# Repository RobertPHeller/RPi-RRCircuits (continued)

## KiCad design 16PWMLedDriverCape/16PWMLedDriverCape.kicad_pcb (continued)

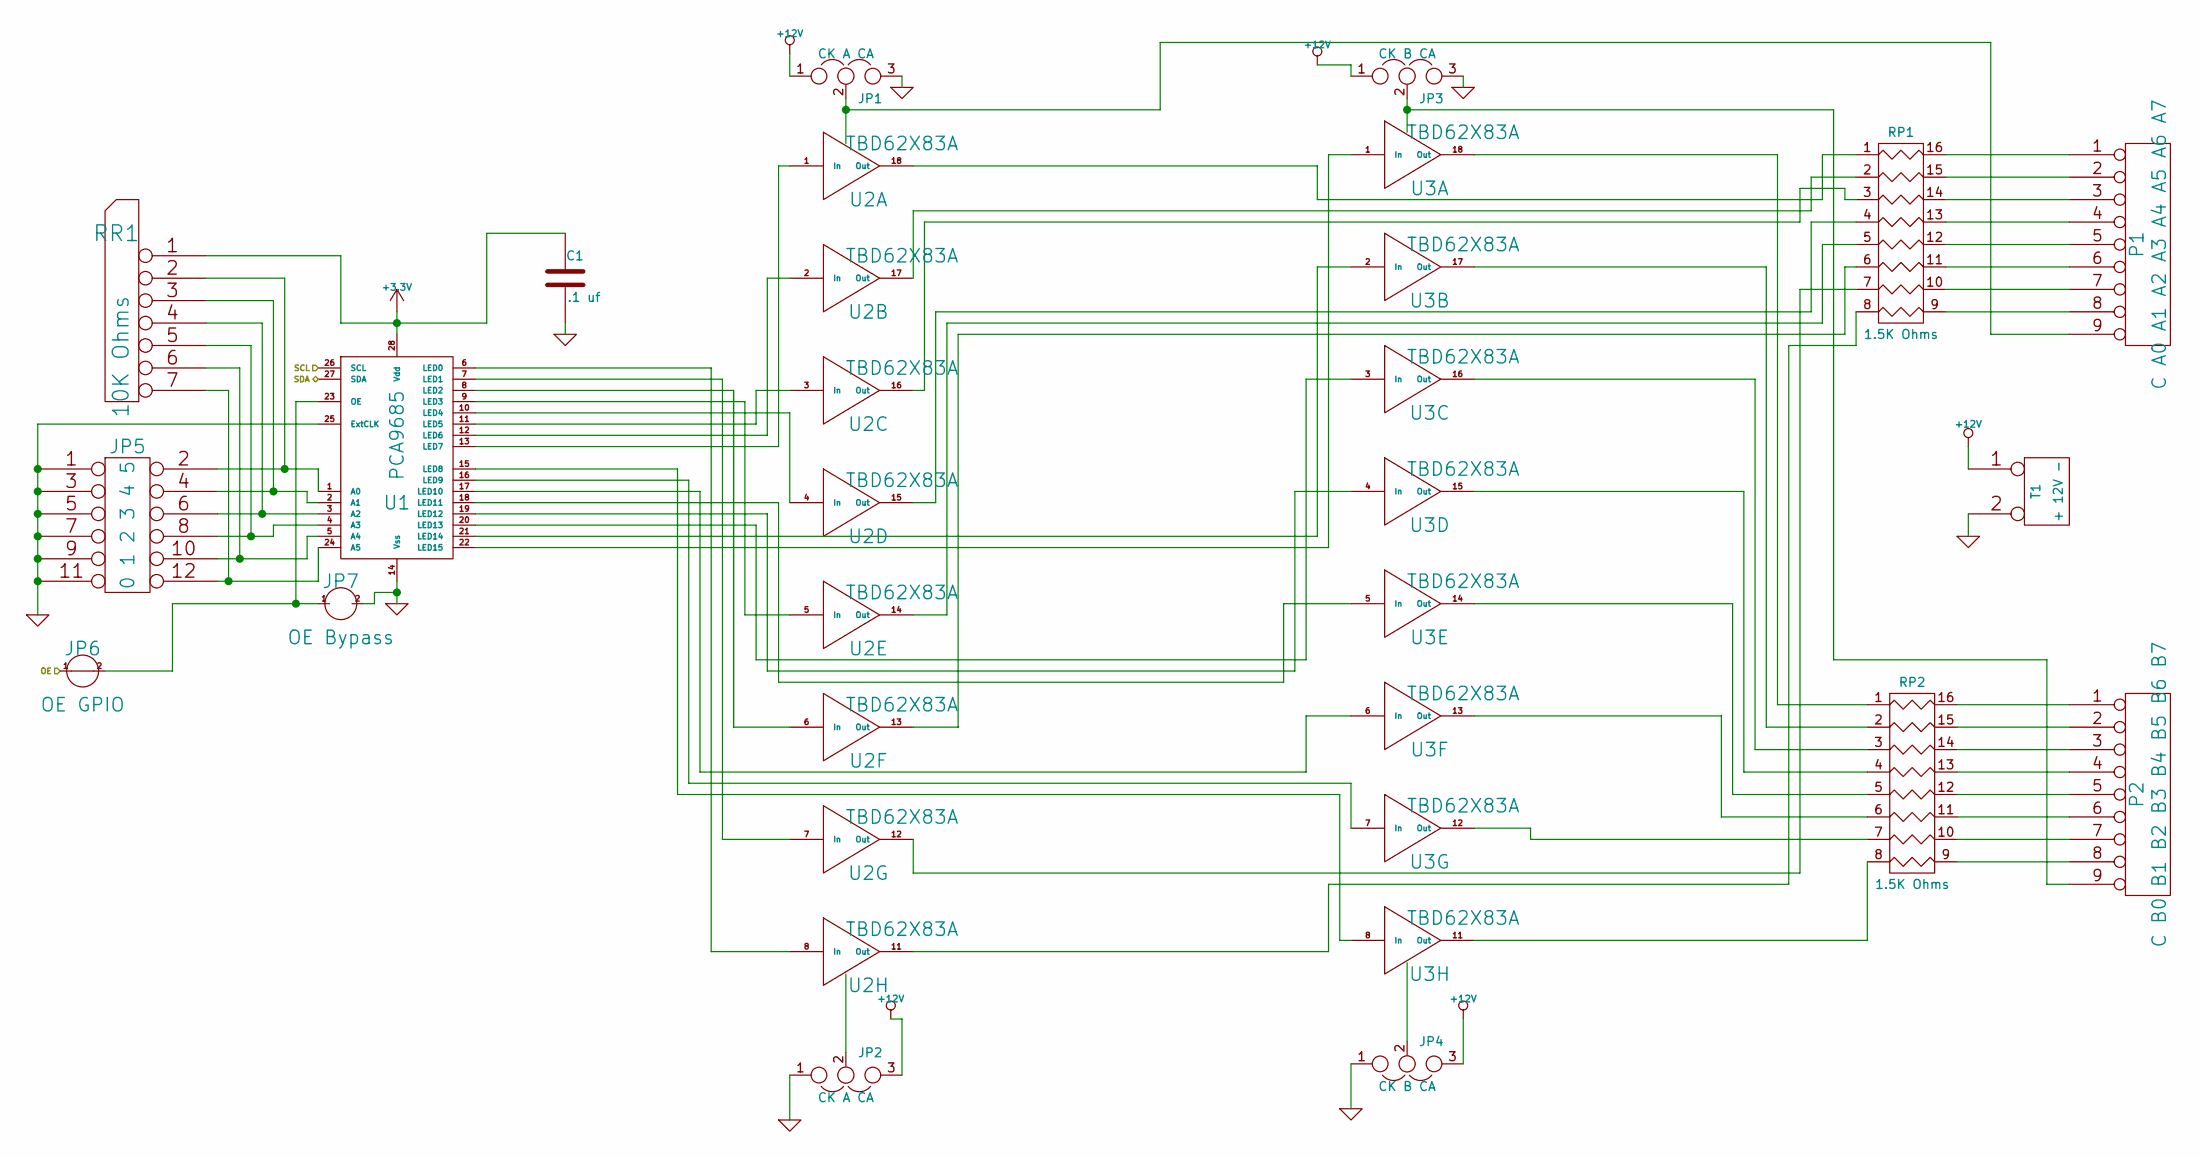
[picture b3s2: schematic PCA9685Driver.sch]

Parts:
C1: .1 uf
JP1, JP2: CK A CA
JP3, JP4: CK B CA
JP5: 0 1 2 3 4 5
JP6: OE GPIO
JP7: OE Bypass
P1: C A0 A1 A2 A3 A4 A5 A6 A7
P2: C B0 B1 B2 B3 B4 B5 B6 B7
RP1, RP2: 1.5K Ohms
RR1: 10K Ohms
T1: + 12V -
U1: PCA9685
U2, U3: TBD62X83A

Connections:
+3.3V: C1.1, RR1.1 (COM), U1.28 (Vdd); also elsewhere on the board
+12V: JP1.1, JP2.3, JP3.1, JP4.3, T1.1
/PCA9685 Driver/OE: JP6.1; also elsewhere on the board
/PCA9685 Driver/SCL: U1.26 (SCL); also elsewhere on the board
/PCA9685 Driver/SDA: U1.27 (SDA); also elsewhere on the board
GND: C1.2, JP1.3, JP2.1, JP3.3, JP4.1, JP5.1, JP5.3, JP5.5, JP5.7, JP5.9, JP5.11, JP7.2, T1.2 (PM), U1.14 (Vss), U1.25 (ExtCLK); also elsewhere on the board
unnamed: RP2.8, U3.11 (Out)
unnamed: RP2.7, U3.12 (Out)
unnamed: RP2.6, U3.13 (Out)
unnamed: RP2.5, U3.14 (Out)
unnamed: RP2.4, U3.15 (Out)
unnamed: JP5.2, RR1.2, U1.1 (A0)
unnamed: JP5.4, RR1.3, U1.2 (A1)
unnamed: JP5.10, RR1.6, U1.5 (A4)
unnamed: JP5.8, RR1.5, U1.4 (A3)
unnamed: JP5.12, RR1.7, U1.24 (A5)
unnamed: RP1.4, U2.15 (Out)
unnamed: RP1.3, U2.16 (Out)
unnamed: RP1.2, U2.17 (Out)
unnamed: RP1.1, U2.18 (Out)
unnamed: P2.8, RP2.9 (R8)
unnamed: P2.7, RP2.10 (R7)
unnamed: P2.6, RP2.11 (R6)
unnamed: P2.5, RP2.12 (R5)
unnamed: P2.4, RP2.13 (R4)
unnamed: RP2.3, U3.16 (Out)
unnamed: RP2.2, U3.17 (Out)
unnamed: RP2.1, U3.18 (Out)
unnamed: RP1.8, U2.11 (Out)
unnamed: RP1.7, U2.12 (Out)
unnamed: RP1.6, U2.13 (Out)
unnamed: RP1.5, U2.14 (Out)
unnamed: U1.19 (LED12), U3.4 (In)
unnamed: U1.11 (LED5), U2.3 (In)
unnamed: U1.8 (LED2), U2.6 (In)
unnamed: U1.10 (LED4), U2.4 (In)
unnamed: U1.21 (LED14), U3.2 (In)
unnamed: U1.12 (LED6), U2.2 (In)
unnamed: U1.17 (LED10), U3.6 (In)
unnamed: U1.9 (LED3), U2.5 (In)
unnamed: U1.22 (LED15), U3.1 (In)
unnamed: JP6.2, JP7.1, U1.23 (OE)
unnamed: JP5.6, RR1.4, U1.3 (A2)
unnamed: JP1.2, P1.9, U2.10 (OC)
unnamed: JP2.2, U2.9 (IC)
unnamed: P2.1, RP2.16 (R1)
unnamed: JP3.2, P2.9, U3.10 (OC)
unnamed: P2.3, RP2.14 (R3)
unnamed: P2.2, RP2.15 (R2)
unnamed: JP4.2, U3.9 (IC)
unnamed: U1.16 (LED9), U3.7 (In)
unnamed: U1.18 (LED11), U3.5 (In)
unnamed: U1.20 (LED13), U3.3 (In)
unnamed: P1.1, RP1.16 (R1)
unnamed: P1.2, RP1.15 (R2)
unnamed: P1.3, RP1.14 (R3)
unnamed: P1.4, RP1.13 (R4)
unnamed: P1.5, RP1.12 (R5)
unnamed: P1.6, RP1.11 (R6)
unnamed: P1.7, RP1.10 (R7)
unnamed: P1.8, RP1.9 (R8)
unnamed: U1.15 (LED8), U3.8 (In)
unnamed: U1.7 (LED1), U2.7 (In)
unnamed: U1.13 (LED7), U2.1 (In)
unnamed: U1.6 (LED0), U2.8 (In)

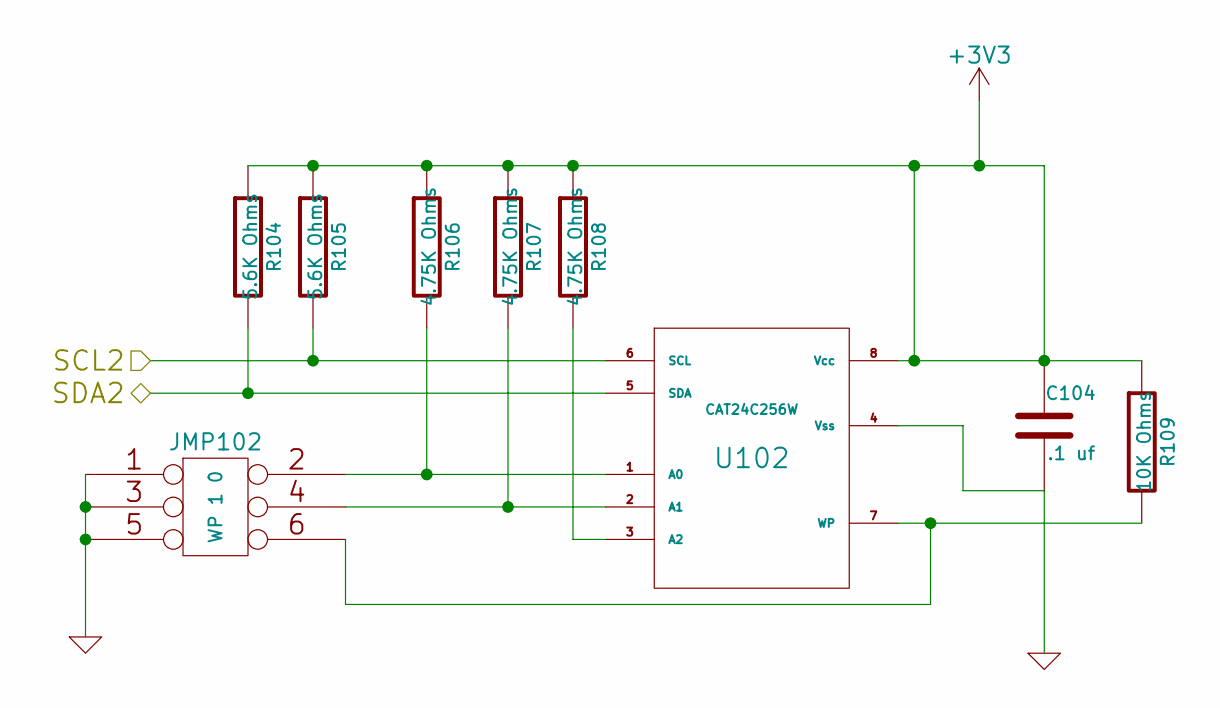
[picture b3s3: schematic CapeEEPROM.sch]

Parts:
C104: .1 uf
JMP102: WP 1 0
R104, R105: 5.6K Ohms
R106, R107, R108: 4.75K Ohms
R109: 10K Ohms
U102: CAT24C256W

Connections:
+3.3V: C104.1, R104.1, R105.1, R106.1, R107.1, R108.1, R109.1, U102.8 (Vcc); also elsewhere on the board
/Cape EEProm/SCL2: R105.2, U102.6 (SCL); also elsewhere on the board
/Cape EEProm/SDA2: R104.2, U102.5 (SDA); also elsewhere on the board
GND: C104.2, JMP102.1, JMP102.3, JMP102.5, U102.4 (Vss); also elsewhere on the board
unnamed: R108.2, U102.3 (A2)
unnamed: JMP102.4, R107.2, U102.2 (A1)
unnamed: JMP102.2, R106.2, U102.1 (A0)
unnamed: JMP102.6, R109.2, U102.7 (WP)

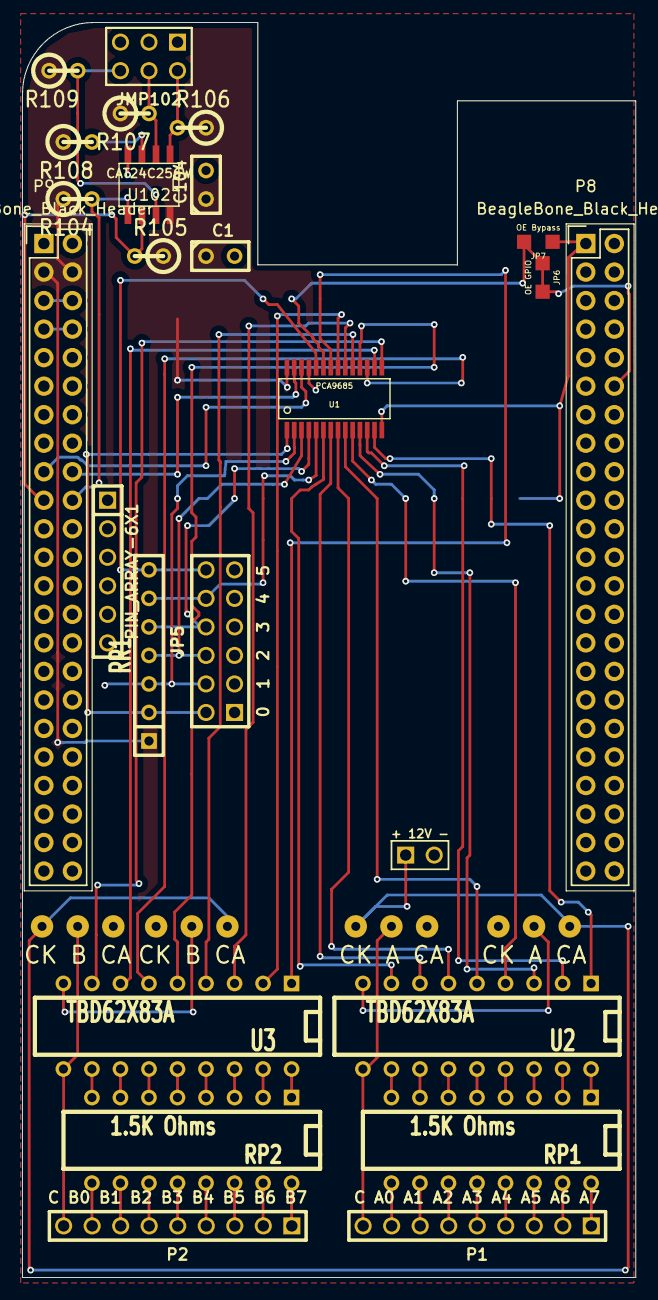
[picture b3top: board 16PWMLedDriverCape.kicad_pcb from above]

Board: 2 copper layers, 54.6 x 111.8 mm, 29 parts (0 on the bottom side), 73 nets.

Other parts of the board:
PIN_ARRAY-6X1: Val**; PIN_ARRAY-6X1

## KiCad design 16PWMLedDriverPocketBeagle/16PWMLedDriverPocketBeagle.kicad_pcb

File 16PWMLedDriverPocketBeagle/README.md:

# 16PWMLedDriverPocketBeagle

This is a PCA9685 with two octal buffers meant to drive 16 LEDs (such as
signal lamps). This board is much like 16DriverOutputCape, but uses a PWM chip
to allow for special effects and allows for brightness adjustment. Has address
jumpers for the PCA9685, includes a CAN transceiver with LCC network
connectors (RJ45s), 5V power supply for the PocketBeagle, and uses LCC power
for the LEDS. It uses female headers for the PocketBeagle (presumes male pin
headers soldered to the underside of the PocketBeagle).

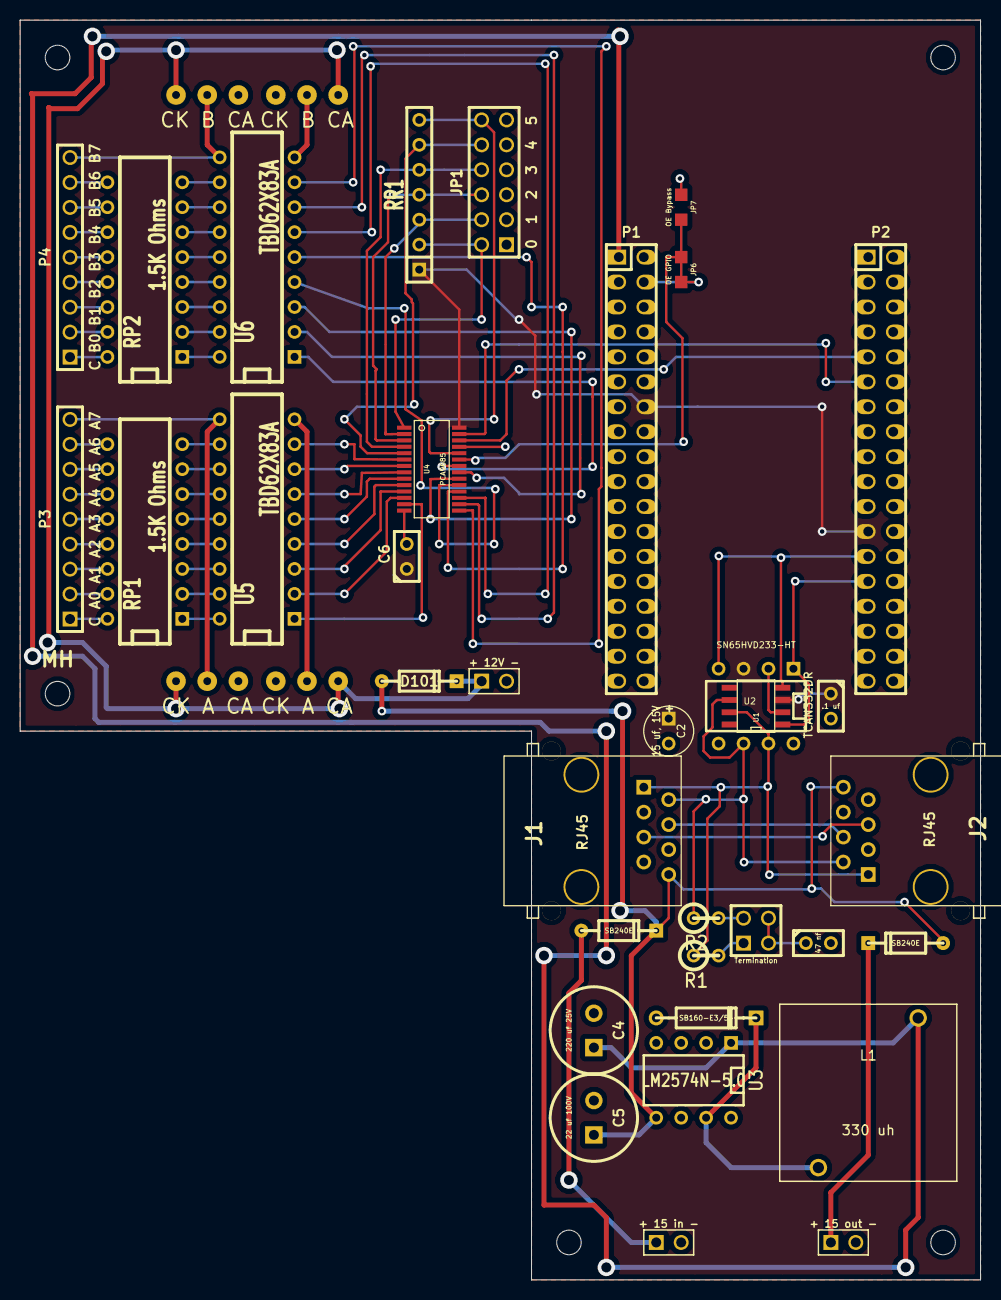
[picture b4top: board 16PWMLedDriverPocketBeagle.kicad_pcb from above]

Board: 2 copper layers, 97.8 x 128.3 mm, 44 parts (0 on the bottom side), 79 nets.

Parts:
C1, C6: .1 uf; C1
C2: 15 uf, 15V; C1V5
C3: 47 nf; C1
C4: 220 uf 25V; C1-3V8
C5: 22 uf 100V; C1-3V8
D1, D2, D101: SB240E; DO-35
D3: SB160-E3/54; DO-41
J1, J2: RJ45; RJ45_8N-S
JMP1: Termination; PIN_ARRAY_2X2
JP1: 0 1 2 3 4 5; pin_array_6x2
JP2, JP3: CK A CA; 3PosJumper
JP4, JP5: CK B CA; 3PosJumper
JP6: OE GPIO; Closed_Jumper
JP7: OE Bypass; Open_Jumper
L1: 330 uh; PE-LowProfile
MH: MountingHole_2-5mm_RevA_Date21Jun2010
MH#2, MH#3, MH#4, MH#5: MountingHole_2-5mm_RevA_Date21Jun2010
P1: POCKETBEAGLE-P1; pin_socket_18x2
P2: POCKETBEAGLE-P2; pin_socket_18x2
P3: C A0 A1 A2 A3 A4 A5 A6 A7; ScrewTerm_2.54-9
P4: C B0 B1 B2 B3 B4 B5 B6 B7; ScrewTerm_2.54-9
R1, R2: 60 Ohms; R1
RP1, RP2: 1.5K Ohms; DIP-16__300
RR1: 10K Ohms; SIL-7
T1: + 15 in -; ScrewTerm2.54-2
T2: + 15 out -; ScrewTerm2.54-2
T101: + 12V -; ScrewTerm2.54-2
U1: TCAN332DR; SOIC-8_N
U2: SN65HVD233-HT; DIP-8__300
U3: LM2574N-5.0; DIP-8__300
U4: PCA9685; tssop-28
U5, U6: TBD62X83A; DIP-18__300

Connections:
+3.3V: C1.1, C2.1, C6.1, P1.14, P2.23, RR1.1, U1.3, U2.3, U4.28
+5V: C4.1, L1.1, P1.1, U3.1
+12V: D101.2, JP2.1, JP3.3, JP4.1, JP5.3, T101.1
/CAN1_RX: P2.25, U1.4, U2.4
/CAN1_TX: P2.27, U1.1, U2.1
/CANH: J1.1, J2.1, R1.1, U1.7, U2.7
/CANL: J1.2, J2.2, R2.1, U1.6, U2.6
/PCA9685 Driver/OE: JP6.1, P1.4
/PCA9685 Driver/SCL: P2.9, U4.26
/PCA9685 Driver/SDA: P2.11, U4.27
/Power Supply/12-15 Volt input: C5.1, D1.2, D2.1, D101.1, J1.8, J2.8, U3.5
GND: C1.2, C2.2, C3.2, C4.2, C5.2, C6.2, D3.1, J1.3, J1.6, J1.7, J2.3, J2.6, J2.7, JP1.1, JP1.3, JP1.5, JP1.7, JP1.9, JP1.11, JP2.3, JP3.1, JP4.3, JP5.1, JP7.2, P1.15, P1.16, P1.22, P2.15, P2.21, T1.2, T2.2, T101.2, U1.2, U2.2, U2.5, U2.8, U3.2, U3.3, U3.4, U4.14, U4.25
unnamed: C3.1, JMP1.3, JMP1.4
unnamed: JMP1.1, R1.2
unnamed: JMP1.2, R2.2
unnamed: J1.5, J2.5
unnamed: J1.4, J2.4
unnamed: D2.2, T2.1
unnamed: D1.1, T1.1
unnamed: D3.2, L1.2, U3.7
unnamed: JP4.2, P4.9, U6.10
unnamed: P3.1, RP1.16
unnamed: P3.2, RP1.15
unnamed: P3.3, RP1.14
unnamed: P3.4, RP1.13
unnamed: P3.5, RP1.12
unnamed: P3.6, RP1.11
unnamed: P3.7, RP1.10
unnamed: P3.8, RP1.9
unnamed: JP2.2, P3.9, U5.10
unnamed: JP3.2, U5.9
unnamed: JP5.2, U6.9
unnamed: U4.15, U6.8
unnamed: RP1.3, U5.16
unnamed: RP1.2, U5.17
unnamed: RP1.1, U5.18
unnamed: P4.8, RP2.9
unnamed: P4.7, RP2.10
unnamed: P4.6, RP2.11
unnamed: P4.5, RP2.12
unnamed: P4.4, RP2.13
unnamed: P4.3, RP2.14
unnamed: P4.2, RP2.15
unnamed: P4.1, RP2.16
unnamed: U4.21, U6.2
unnamed: U4.22, U6.1
unnamed: U4.6, U5.8
unnamed: U4.8, U5.6
unnamed: U4.9, U5.5
unnamed: U4.10, U5.4
unnamed: U4.11, U5.3
unnamed: U4.12, U5.2
unnamed: U4.13, U5.1
unnamed: U4.16, U6.7
unnamed: U4.7, U5.7
unnamed: U4.17, U6.6
unnamed: U4.18, U6.5
unnamed: U4.19, U6.4
unnamed: U4.20, U6.3
unnamed: JP1.4, RR1.3, U4.2
unnamed: JP1.6, RR1.4, U4.3
unnamed: JP1.8, RR1.5, U4.4
unnamed: JP1.10, RR1.6, U4.5
unnamed: JP1.12, RR1.7, U4.24
unnamed: JP6.2, JP7.1, U4.23
unnamed: JP1.2, RR1.2, U4.1
unnamed: RP2.2, U6.17
unnamed: RP2.1, U6.18
unnamed: RP1.8, U5.11
unnamed: RP1.7, U5.12
unnamed: RP1.6, U5.13
unnamed: RP1.5, U5.14
unnamed: RP1.4, U5.15
unnamed: RP2.8, U6.11
unnamed: RP2.7, U6.12
unnamed: RP2.6, U6.13
unnamed: RP2.5, U6.14
unnamed: RP2.4, U6.15
unnamed: RP2.3, U6.16

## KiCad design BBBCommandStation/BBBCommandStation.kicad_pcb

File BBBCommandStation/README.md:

# BBBCommandStation

Early BeagleBone Black LCC/DCC Command Station board set -- two boards, a cape 
and a power board.  Does not include RailComm support.

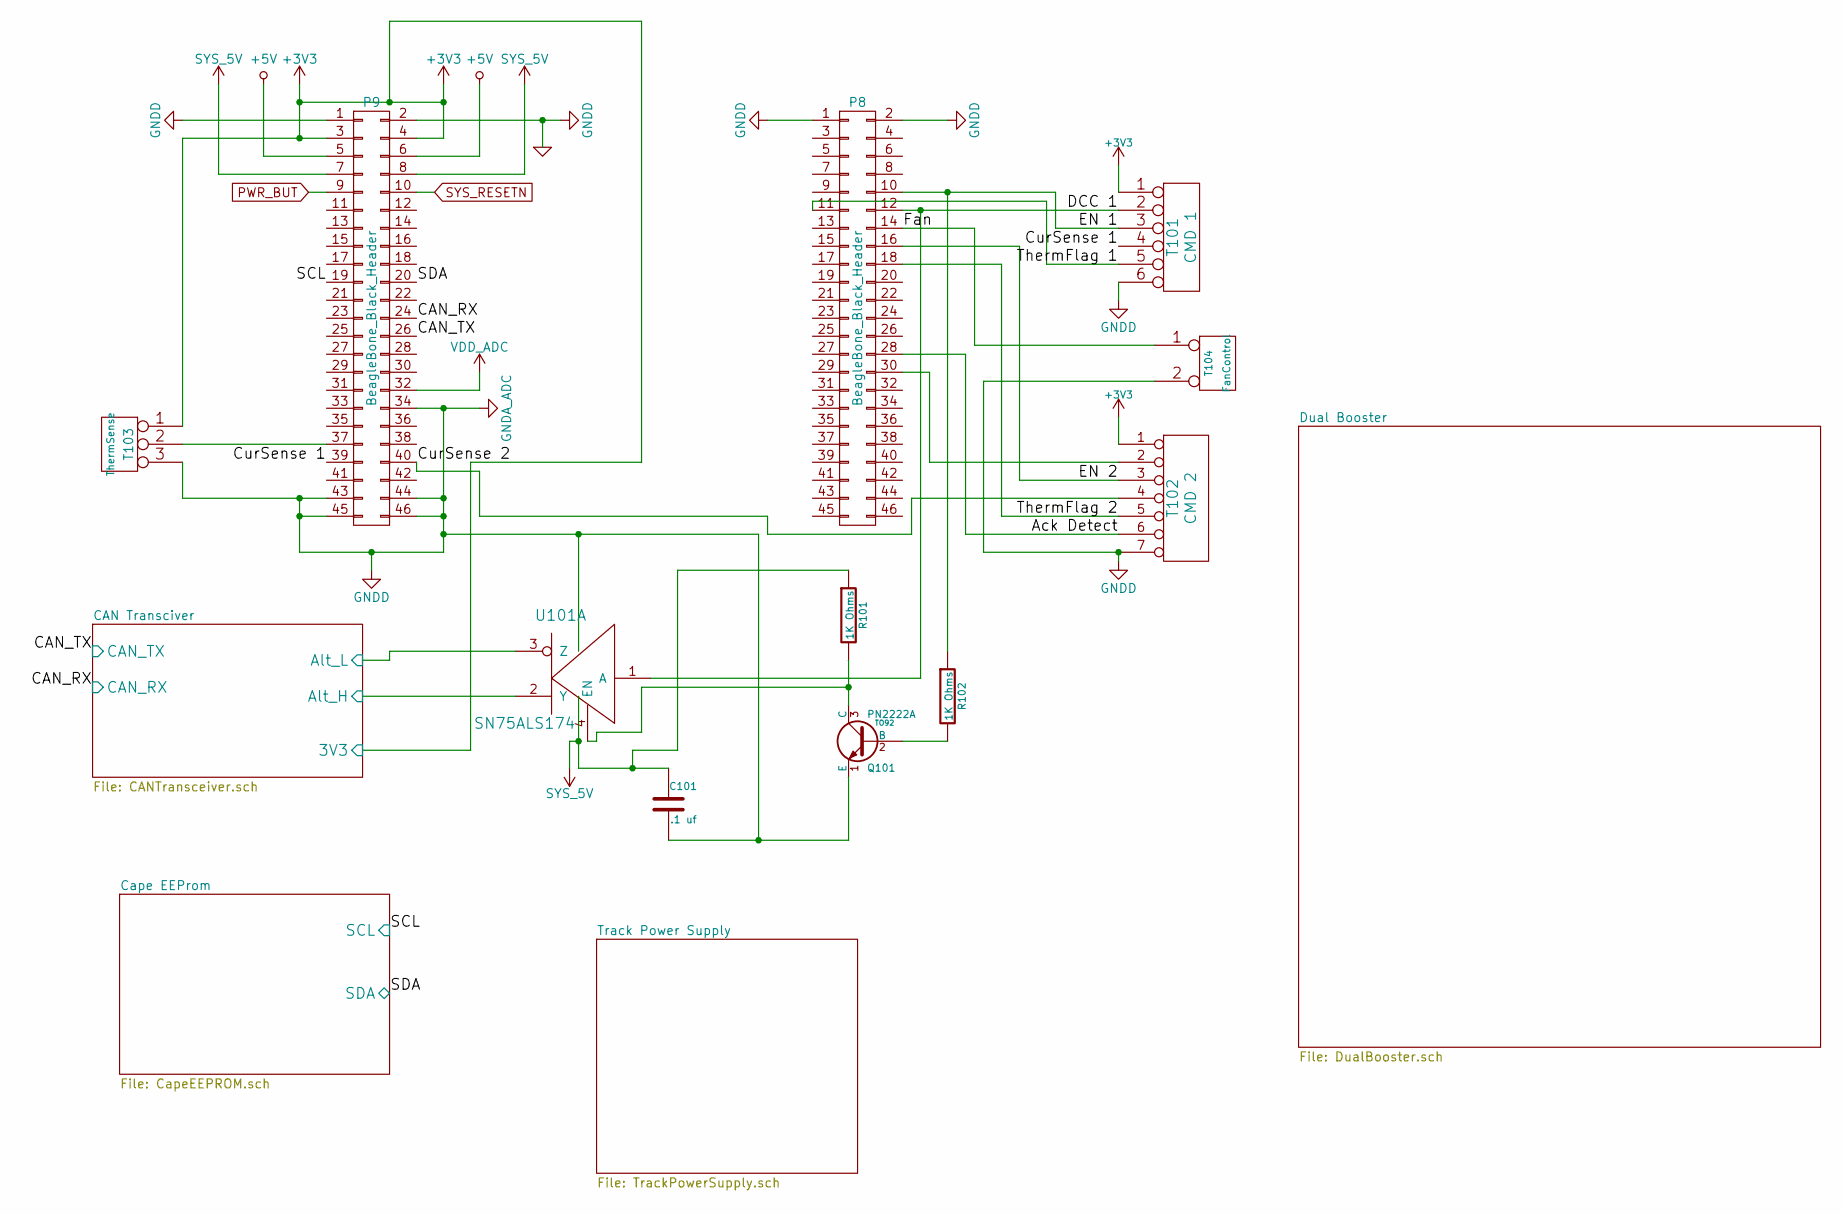
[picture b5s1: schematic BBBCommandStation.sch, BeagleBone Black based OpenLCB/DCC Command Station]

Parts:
C101: .1 uf
P8, P9: BeagleBone_Black_Header; Socket_BeagleBone_Black
Q101: PN2222A; TO92
R101, R102: 1K Ohms
T101: CMD 1
T102: CMD 2
T103: ThermSense
T104: FanControl
U101: SN75ALS174

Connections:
+3V3: P9.3, P9.4, T101.1, T102.1, T103.1; also elsewhere on the board
+5V: P9.5, P9.6
/Ack Detect: P8.28, T102.6
/CAN Transciver/Alt_H: U101.2 (Y); also elsewhere on the board
/CAN Transciver/Alt_L: U101.3 (Z); also elsewhere on the board
/CAN Transciver/CAN_RX: P9.24; also elsewhere on the board
/CAN Transciver/CAN_TX: P9.26; also elsewhere on the board
/Cape EEProm/SCL: P9.19; also elsewhere on the board
/Cape EEProm/SDA: P9.20; also elsewhere on the board
/CurSense 1: P9.39, T101.4
/CurSense 2: P9.40, T102.4
/DCC 1: P8.12, T101.2, U101.1 (A)
/EN 1: P8.10, R102.1, T101.3
/EN 2: P8.16, T102.3
/Fan: P8.14, T104.1
/ThermFlag 1: P8.11, T101.5
/ThermFlag 2: P8.18, T102.5
GND: C101.2, P8.1, P8.2, P9.1, P9.2, P9.34, P9.43, P9.44, P9.45, P9.46, Q101.1 (E), T101.6, T102.7, T103.3, T104.2 (PM), U101.8 (Gnd); also elsewhere on the board
unnamed: Q101.3 (C), R101.2, U101.4 (EN)
unnamed: P9.37, T103.2 (PM)
unnamed: P8.30, T102.2
unnamed: Q101.2 (B), R102.2
SYS_5V: C101.1, P9.7, P9.8, R101.1, U101.16 (Vcc)

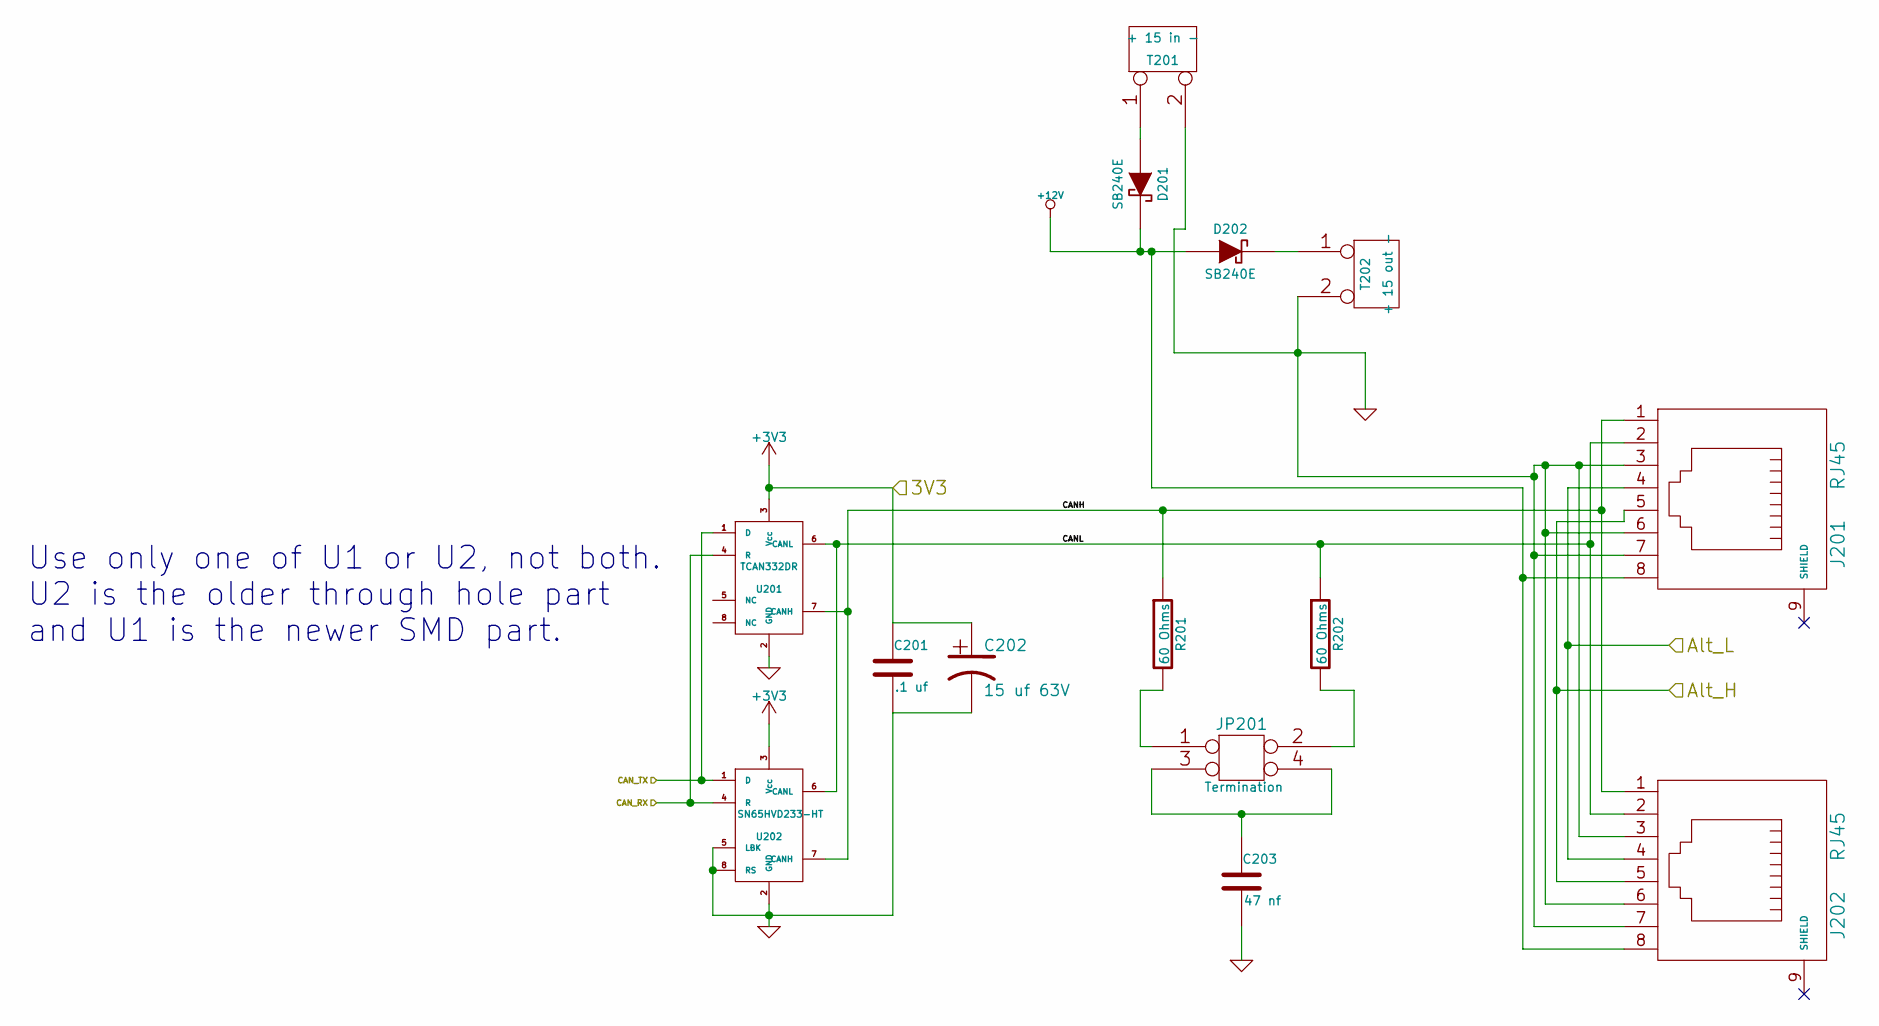
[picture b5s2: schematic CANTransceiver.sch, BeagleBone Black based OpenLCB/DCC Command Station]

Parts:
C201: .1 uf; Mouser Part Number 21RZ310-RC
C202: 15 uf 63V; Mouser Part Number 710-860080773002
C203: 47 nf; Mouser Part Number 75-1C10Z5U473M050B
D201, D202: SB240E; Mouser Part Number 625-SB240-E3
J201, J202: RJ45; Mouser Part Number 710-615008144221
JP201: Termination; Mouser Part Number 649-67997-404HLF
R201, R202: 60 Ohms; Mouser Part Number 71-RN60C60R0B/R
T201: + 15 in -; Mouser Part Number 651-1725656
T202: + 15 out -; Mouser Part Number 651-1725656
U201: TCAN332DR; Mouser Part Number 595-TCAN332DR
U202: SN65HVD233-HT; Mouser Part Number 595-SN65HVD233SJD

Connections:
+3V3: C201.1, C202.1, U201.3 (Vcc), U202.3 (Vcc); also elsewhere on the board
+12V: D201.2 (K), D202.1 (A), J201.8, J202.8
/CAN Transciver/Alt_H: J201.5, J202.5; also elsewhere on the board
/CAN Transciver/Alt_L: J201.4, J202.4; also elsewhere on the board
/CAN Transciver/CANH: J201.1, J202.1, R201.1, U201.7 (CANH), U202.7 (CANH)
/CAN Transciver/CANL: J201.2, J202.2, R202.1, U201.6 (CANL), U202.6 (CANL)
/CAN Transciver/CAN_RX: U201.4 (R), U202.4 (R); also elsewhere on the board
/CAN Transciver/CAN_TX: U201.1 (D), U202.1 (D); also elsewhere on the board
GND: C201.2, C202.2, C203.2, J201.3, J201.6, J201.7, J202.3, J202.6, J202.7, T201.2 (PM), T202.2 (PM), U201.2 (GND), U202.2 (GND), U202.5 (LBK), U202.8 (RS); also elsewhere on the board
unnamed: D201.1 (A), T201.1
unnamed: D202.2 (K), T202.1
unnamed: JP201.1, R201.2
unnamed: JP201.2, R202.2
unnamed: C203.1, JP201.3, JP201.4

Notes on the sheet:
Use only one of U1 or U2, not both. U2 is the older through hole part and U1 is the newer SMD part.

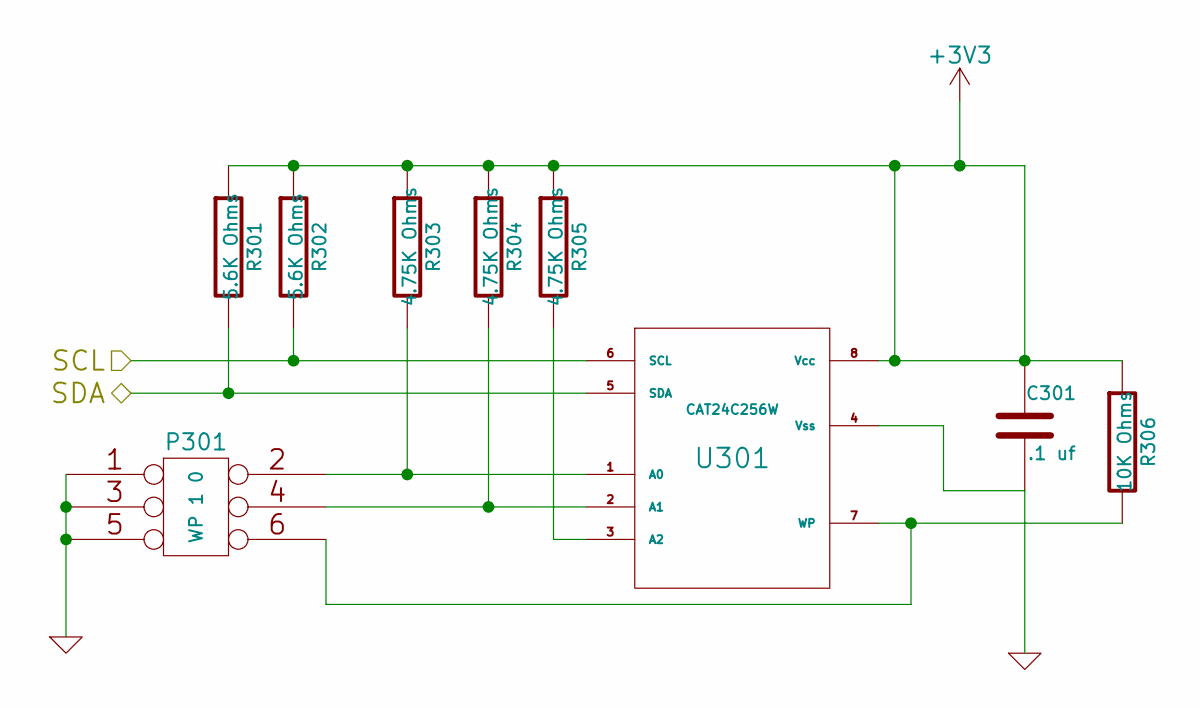
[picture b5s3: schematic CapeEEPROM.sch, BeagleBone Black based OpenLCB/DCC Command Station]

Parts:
C301: .1 uf; Mouser Part Number 581-SR201C104KARTR1
P301: WP 1 0; Mouser Part Number 649-67996-406HLF
R301, R302: 5.6K Ohms; Mouser Part Number 603-CFR-25JR-525K6
R303, R304, R305: 4.75K Ohms; Mouser Part Number 603-CFR-25JR-524K7
R306: 10K Ohms; Mouser Part Number 603-CFR-25JR-5210K
U301: CAT24C256W; Mouser Part Number 698-CAT24C256WI-GT3

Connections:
+3V3: C301.1, R301.1, R302.1, R303.1, R304.1, R305.1, R306.1, U301.8 (Vcc); also elsewhere on the board
/Cape EEProm/SCL: R302.2, U301.6 (SCL); also elsewhere on the board
/Cape EEProm/SDA: R301.2, U301.5 (SDA); also elsewhere on the board
GND: C301.2, P301.1, P301.3, P301.5, U301.4 (Vss); also elsewhere on the board
unnamed: P301.6, R306.2, U301.7 (WP)
unnamed: P301.2, R303.2, U301.1 (A0)
unnamed: P301.4, R304.2, U301.2 (A1)
unnamed: R305.2, U301.3 (A2)

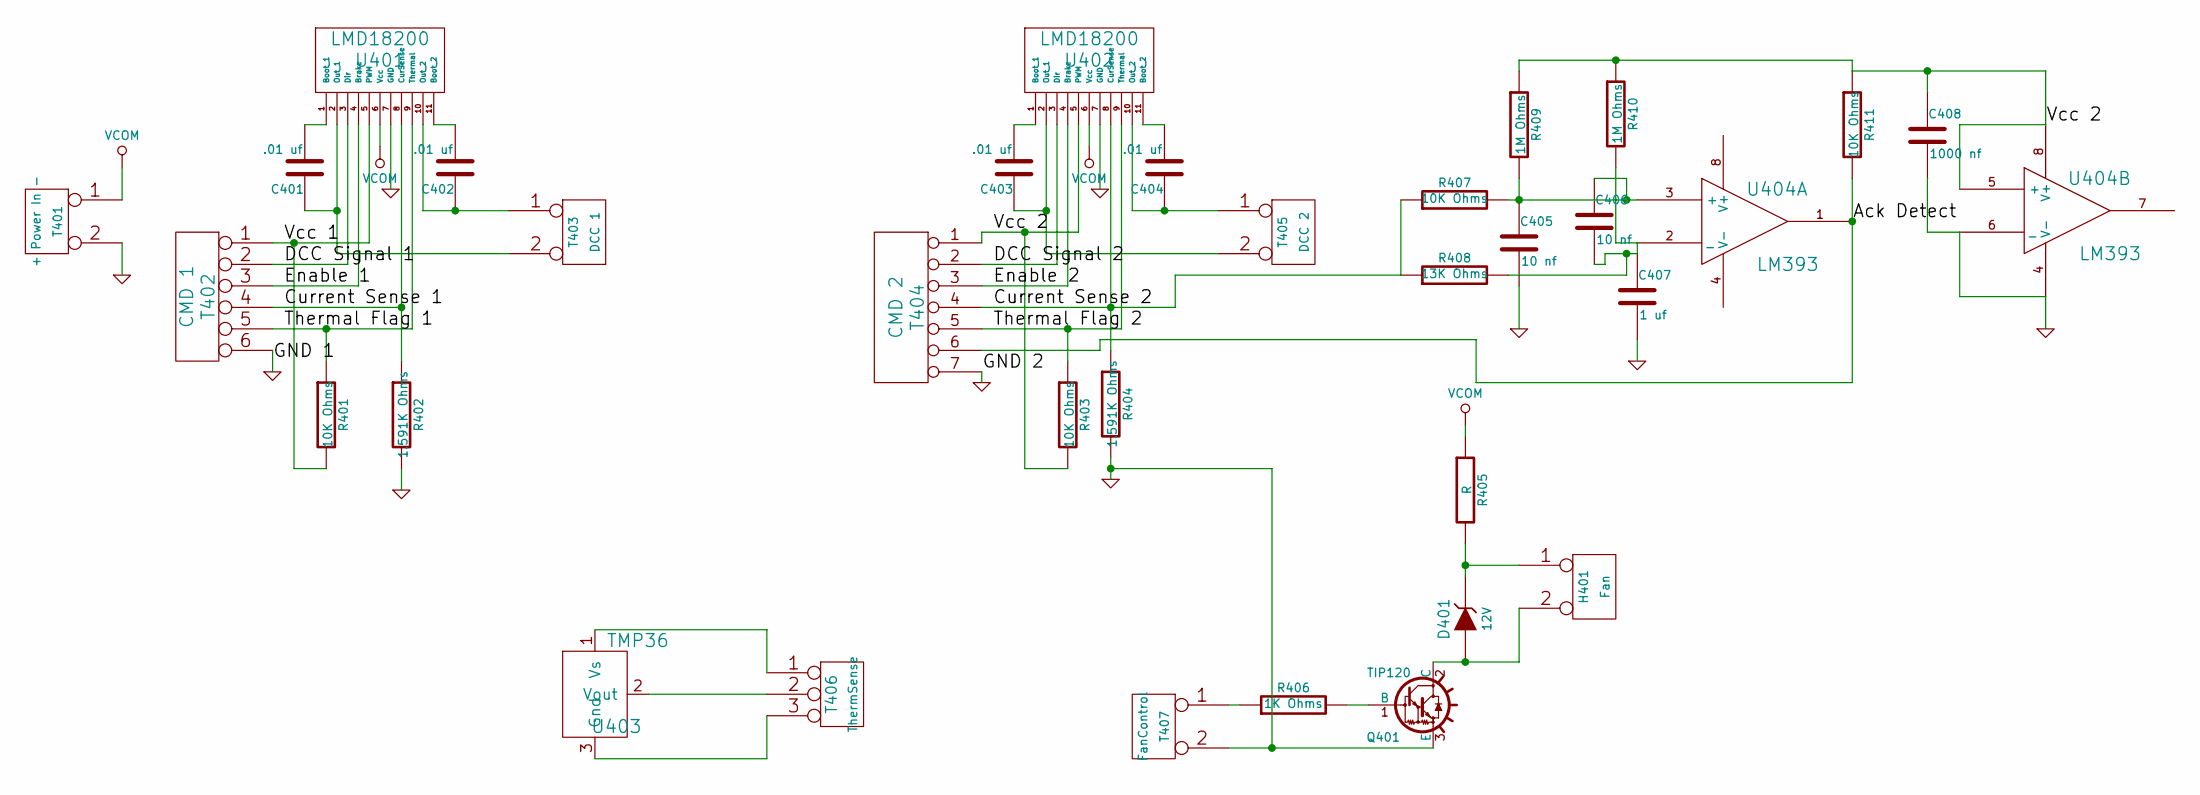
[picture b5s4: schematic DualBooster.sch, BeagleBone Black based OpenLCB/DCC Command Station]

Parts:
C401, C402, C403, C404: .01 uf
C405, C406: 10 nf
C407: 1 uf
C408: 1000 nf
D401: 12V
H401: Fan
Q401: TIP120; TO220
R401, R403, R407, R411: 10K Ohms
R402, R404: 1.591K Ohms
R405: R
R406: 1K Ohms
R408: 13K Ohms
R409, R410: 1M Ohms
T401: + Power In -
T402: CMD 1
T403: DCC 1
T404: CMD 2
T405: DCC 2
T406: ThermSense
T407: FanControl
U401, U402: LMD18200
U403: TMP36
U404: LM393

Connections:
/Dual Booster/Ack Detect: R411.2, T404.6, U404.1
/Dual Booster/Current Sense 1: R402.1, T402.4, U401.8 (CurSense)
/Dual Booster/Current Sense 2: R404.1, R407.1, R408.1, T404.4, U402.8 (CurSense)
/Dual Booster/DCC Signal 1: T402.2, U401.3 (Dir)
/Dual Booster/DCC Signal 2: T404.2, U402.3 (Dir)
/Dual Booster/Enable 1: T402.3, U401.4 (Brake)
/Dual Booster/Enable 2: T404.3, U402.4 (Brake)
/Dual Booster/Thermal Flag 1: R401.1, T402.5, U401.9 (Thermal)
/Dual Booster/Thermal Flag 2: R403.1, T404.5, U402.9 (Thermal)
/Dual Booster/Vcc 1: R401.2, T402.1, U401.5 (PWM)
/Dual Booster/Vcc 2: C408.1, R403.2, R409.1, R410.1, R411.1, T404.1, U402.5 (PWM), U404.5 (+), U404.8 (V+)
AGND: C405.2, C407.2, C408.2, Q401.3 (E), R402.2, R404.2, T401.2 (PM), T402.6, T404.7, T407.2 (PM), U401.7 (GND), U402.7 (GND), U404.4 (V-), U404.6 (_)
unnamed: D401.2 (K), H401.1, R405.2
unnamed: D401.1 (A), H401.2 (PM), Q401.2 (C)
unnamed: R406.1, T407.1
unnamed: Q401.1 (B), R406.2
unnamed: T406.2 (PM), U403.2 (Vout)
unnamed: T406.3, U403.3 (Gnd)
unnamed: T406.1, U403.1 (Vs)
unnamed: C406.2, C407.1, R408.2, R410.2, U404.2 (_)
unnamed: C405.1, C406.1, R407.2, R409.2, U404.3 (+)
unnamed: C404.1, T405.1, U402.10 (Out_2)
unnamed: C403.2, U402.1 (Boot_1)
unnamed: C402.2, U401.11 (Boot_2)
unnamed: C402.1, T403.1, U401.10 (Out_2)
unnamed: C401.2, U401.1 (Boot_1)
unnamed: C401.1, T403.2 (PM), U401.2 (Out_1)
unnamed: C404.2, U402.11 (Boot_2)
unnamed: C403.1, T405.2 (PM), U402.2 (Out_1)
VCOM: R405.1, T401.1, U401.6 (Vcc), U402.6 (Vcc)

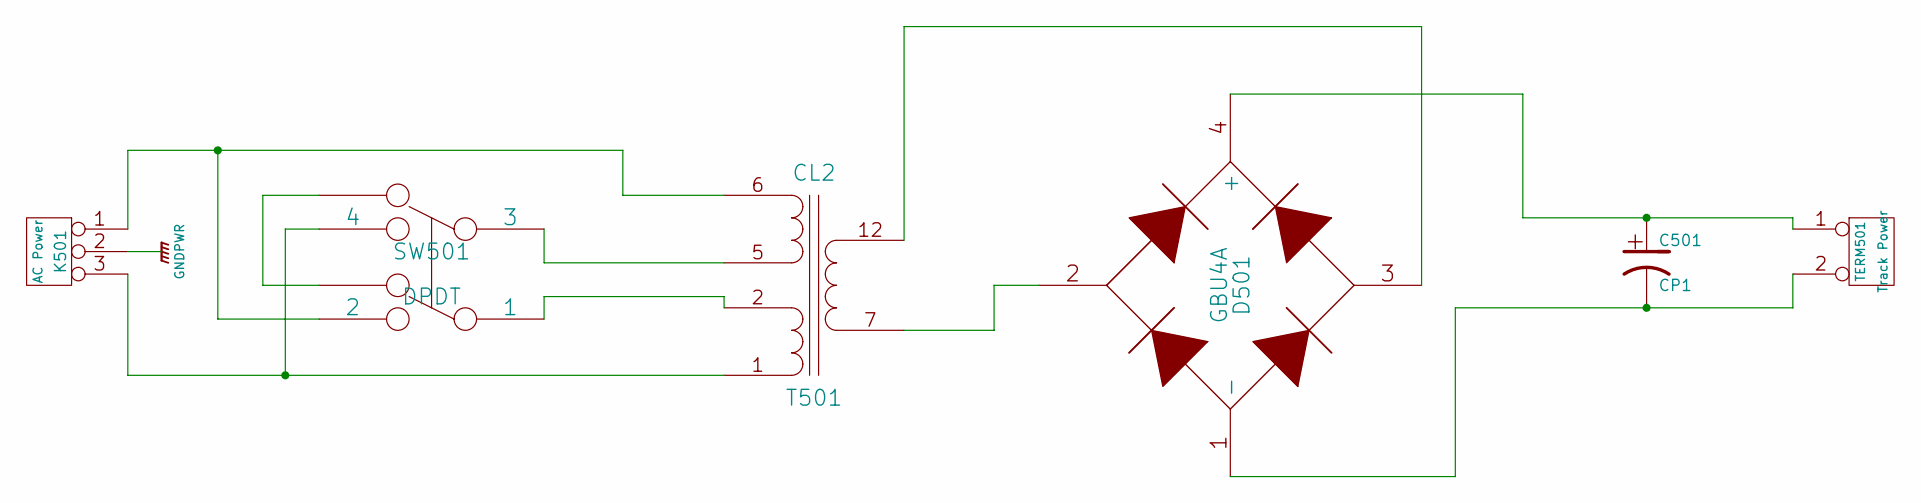
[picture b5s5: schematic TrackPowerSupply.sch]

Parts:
C501: CP1
D501: GBU4A
K501: AC Power
SW501: DPDT
T501: CL2; Mouser Part Number 530-CL2-40-12
TERM501: Track Power

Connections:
unnamed: C501.1, D501.4 (+), TERM501.1
unnamed: C501.2, D501.1 (-), TERM501.2 (PM)
unnamed: D501.2, T501.7 (AA)
unnamed: D501.3, T501.12 (AB)
unnamed: K501.1, SW501.2, T501.6 (SD)
unnamed: K501.3, SW501.4, T501.1 (SA)
unnamed: SW501.1, T501.2 (SB)
unnamed: SW501.3, T501.5 (SC)
unnamed: SW501.6, SW501.7
